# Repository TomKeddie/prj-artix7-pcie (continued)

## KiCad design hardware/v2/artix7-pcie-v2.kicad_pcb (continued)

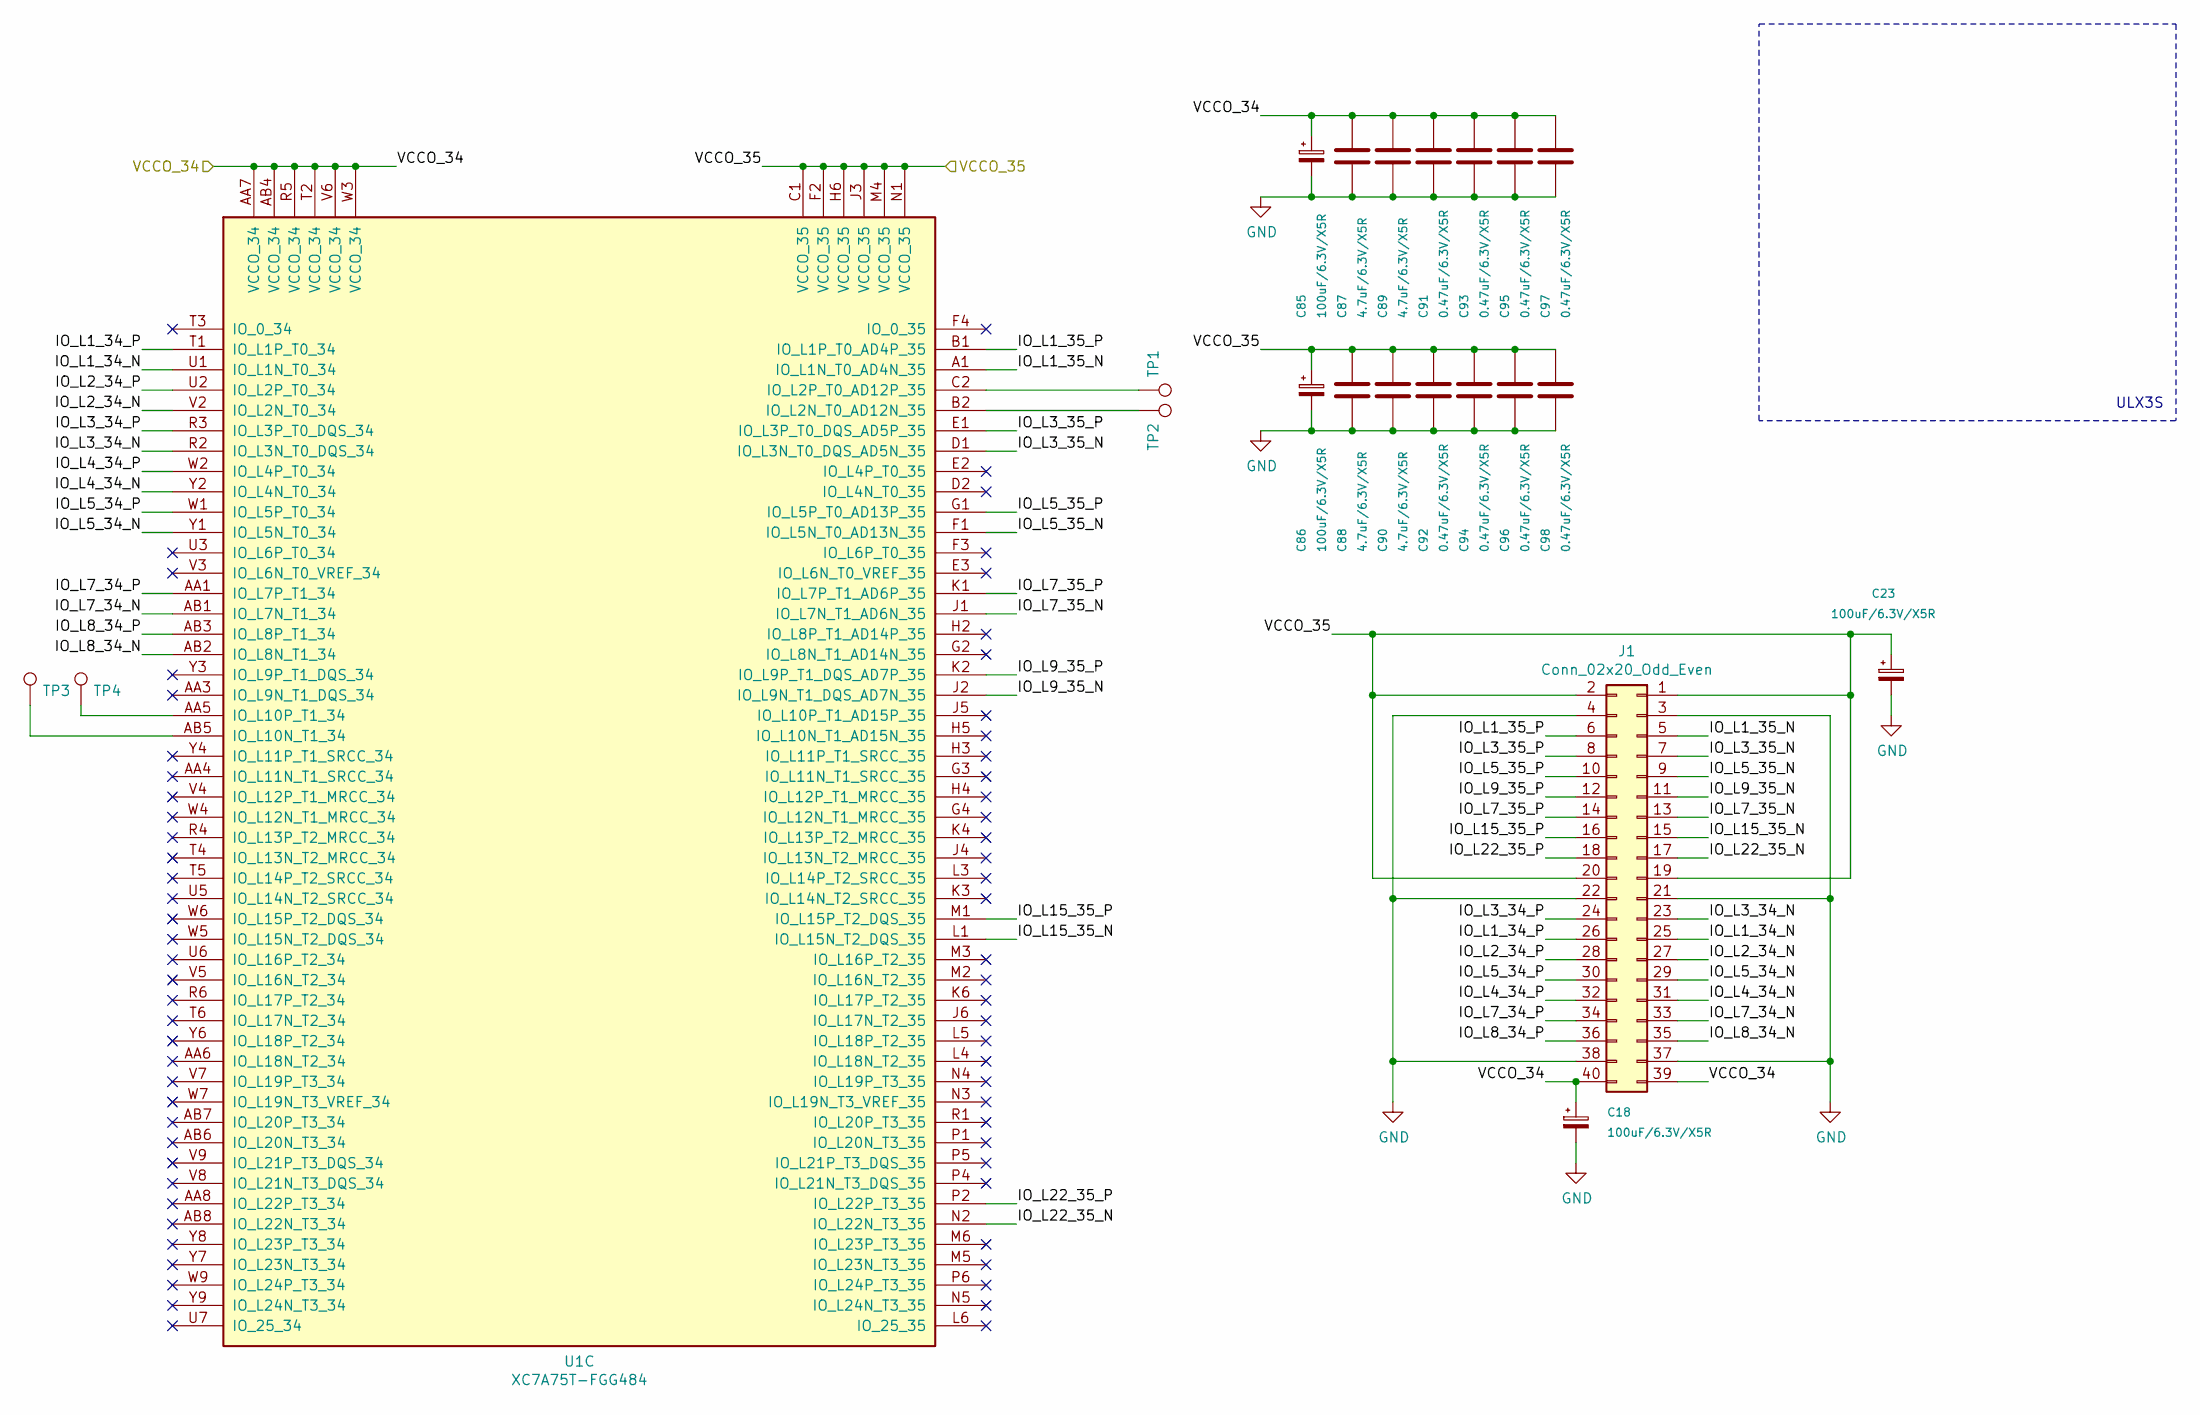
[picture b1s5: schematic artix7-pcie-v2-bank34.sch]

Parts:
C18, C23, C85, C86: 100uF/6.3V/X5R; CP_EIA-3528-15_AVX-H; LCSC C16133
C87, C88, C89, C90: 4.7uF/6.3V/X5R; C_0402_1005Metric; LCSC C23733
C91, C92, C93, C94, C95, C96, C97, C98: 0.47uF/6.3V/X5R; C_0402_1005Metric; LCSC C47339
J1: Conn_02x20_Odd_Even; Socket_Strip_Angled_2x20; LCSC DNP
TP1, TP2, TP3, TP4: TestPoint; TestPoint_Pad_D1.5mm; LCSC DNP
U1: XC7A75T-FGG484; Xilinx_FGG484; LCSC DNP

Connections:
/VCCO_34: C18.1, C23.1, C85.1, C86.1, C87.1, C88.1, C89.1, C90.1, C91.1, C92.1, C93.1, C94.1, C95.1, C96.1, C97.1, C98.1, J1.1, J1.2, J1.19, J1.20, J1.39, J1.40, U1.AA7 (VCCO_34), U1.AB4 (VCCO_34), U1.C1 (VCCO_35), U1.F2 (VCCO_35), U1.H6 (VCCO_35), U1.J3 (VCCO_35), U1.M4 (VCCO_35), U1.N1 (VCCO_35), U1.R5 (VCCO_34), U1.T2 (VCCO_34), U1.V6 (VCCO_34), U1.W3 (VCCO_34); also elsewhere on the board
/artix7-pcie-v2-bank34/IO_L1_34_N: J1.25, U1.U1 (IO_L1N_T0_34)
/artix7-pcie-v2-bank34/IO_L1_34_P: J1.26, U1.T1 (IO_L1P_T0_34)
/artix7-pcie-v2-bank34/IO_L1_35_N: J1.5, U1.A1 (IO_L1N_T0_AD4N_35)
/artix7-pcie-v2-bank34/IO_L1_35_P: J1.6, U1.B1 (IO_L1P_T0_AD4P_35)
/artix7-pcie-v2-bank34/IO_L2_34_N: J1.27, U1.V2 (IO_L2N_T0_34)
/artix7-pcie-v2-bank34/IO_L2_34_P: J1.28, U1.U2 (IO_L2P_T0_34)
/artix7-pcie-v2-bank34/IO_L3_34_N: J1.23, U1.R2 (IO_L3N_T0_DQS_34)
/artix7-pcie-v2-bank34/IO_L3_34_P: J1.24, U1.R3 (IO_L3P_T0_DQS_34)
/artix7-pcie-v2-bank34/IO_L3_35_N: J1.7, U1.D1 (IO_L3N_T0_DQS_AD5N_35)
/artix7-pcie-v2-bank34/IO_L3_35_P: J1.8, U1.E1 (IO_L3P_T0_DQS_AD5P_35)
/artix7-pcie-v2-bank34/IO_L4_34_N: J1.31, U1.Y2 (IO_L4N_T0_34)
/artix7-pcie-v2-bank34/IO_L4_34_P: J1.32, U1.W2 (IO_L4P_T0_34)
/artix7-pcie-v2-bank34/IO_L5_34_N: J1.29, U1.Y1 (IO_L5N_T0_34)
/artix7-pcie-v2-bank34/IO_L5_34_P: J1.30, U1.W1 (IO_L5P_T0_34)
/artix7-pcie-v2-bank34/IO_L5_35_N: J1.9, U1.F1 (IO_L5N_T0_AD13N_35)
/artix7-pcie-v2-bank34/IO_L5_35_P: J1.10, U1.G1 (IO_L5P_T0_AD13P_35)
/artix7-pcie-v2-bank34/IO_L7_34_N: J1.33, U1.AB1 (IO_L7N_T1_34)
/artix7-pcie-v2-bank34/IO_L7_34_P: J1.34, U1.AA1 (IO_L7P_T1_34)
/artix7-pcie-v2-bank34/IO_L7_35_N: J1.13, U1.J1 (IO_L7N_T1_AD6N_35)
/artix7-pcie-v2-bank34/IO_L7_35_P: J1.14, U1.K1 (IO_L7P_T1_AD6P_35)
/artix7-pcie-v2-bank34/IO_L8_34_N: J1.35, U1.AB2 (IO_L8N_T1_34)
/artix7-pcie-v2-bank34/IO_L8_34_P: J1.36, U1.AB3 (IO_L8P_T1_34)
/artix7-pcie-v2-bank34/IO_L9_35_N: J1.11, U1.J2 (IO_L9N_T1_DQS_AD7N_35)
/artix7-pcie-v2-bank34/IO_L9_35_P: J1.12, U1.K2 (IO_L9P_T1_DQS_AD7P_35)
/artix7-pcie-v2-bank34/IO_L15_35_N: J1.15, U1.L1 (IO_L15N_T2_DQS_35)
/artix7-pcie-v2-bank34/IO_L15_35_P: J1.16, U1.M1 (IO_L15P_T2_DQS_35)
/artix7-pcie-v2-bank34/IO_L22_35_N: J1.17, U1.N2 (IO_L22N_T3_35)
/artix7-pcie-v2-bank34/IO_L22_35_P: J1.18, U1.P2 (IO_L22P_T3_35)
GND: C18.2, C23.2, C85.2, C86.2, C87.2, C88.2, C89.2, C90.2, C91.2, C92.2, C93.2, C94.2, C95.2, C96.2, C97.2, C98.2, J1.3, J1.4, J1.21, J1.22, J1.37, J1.38; also elsewhere on the board
unnamed: TP1.1, U1.C2 (IO_L2P_T0_AD12P_35)
unnamed: TP2.1, U1.B2 (IO_L2N_T0_AD12N_35)
unnamed: TP3.1, U1.AB5 (IO_L10N_T1_34)
unnamed: TP4.1, U1.AA5 (IO_L10P_T1_34)

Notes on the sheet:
ULX3S

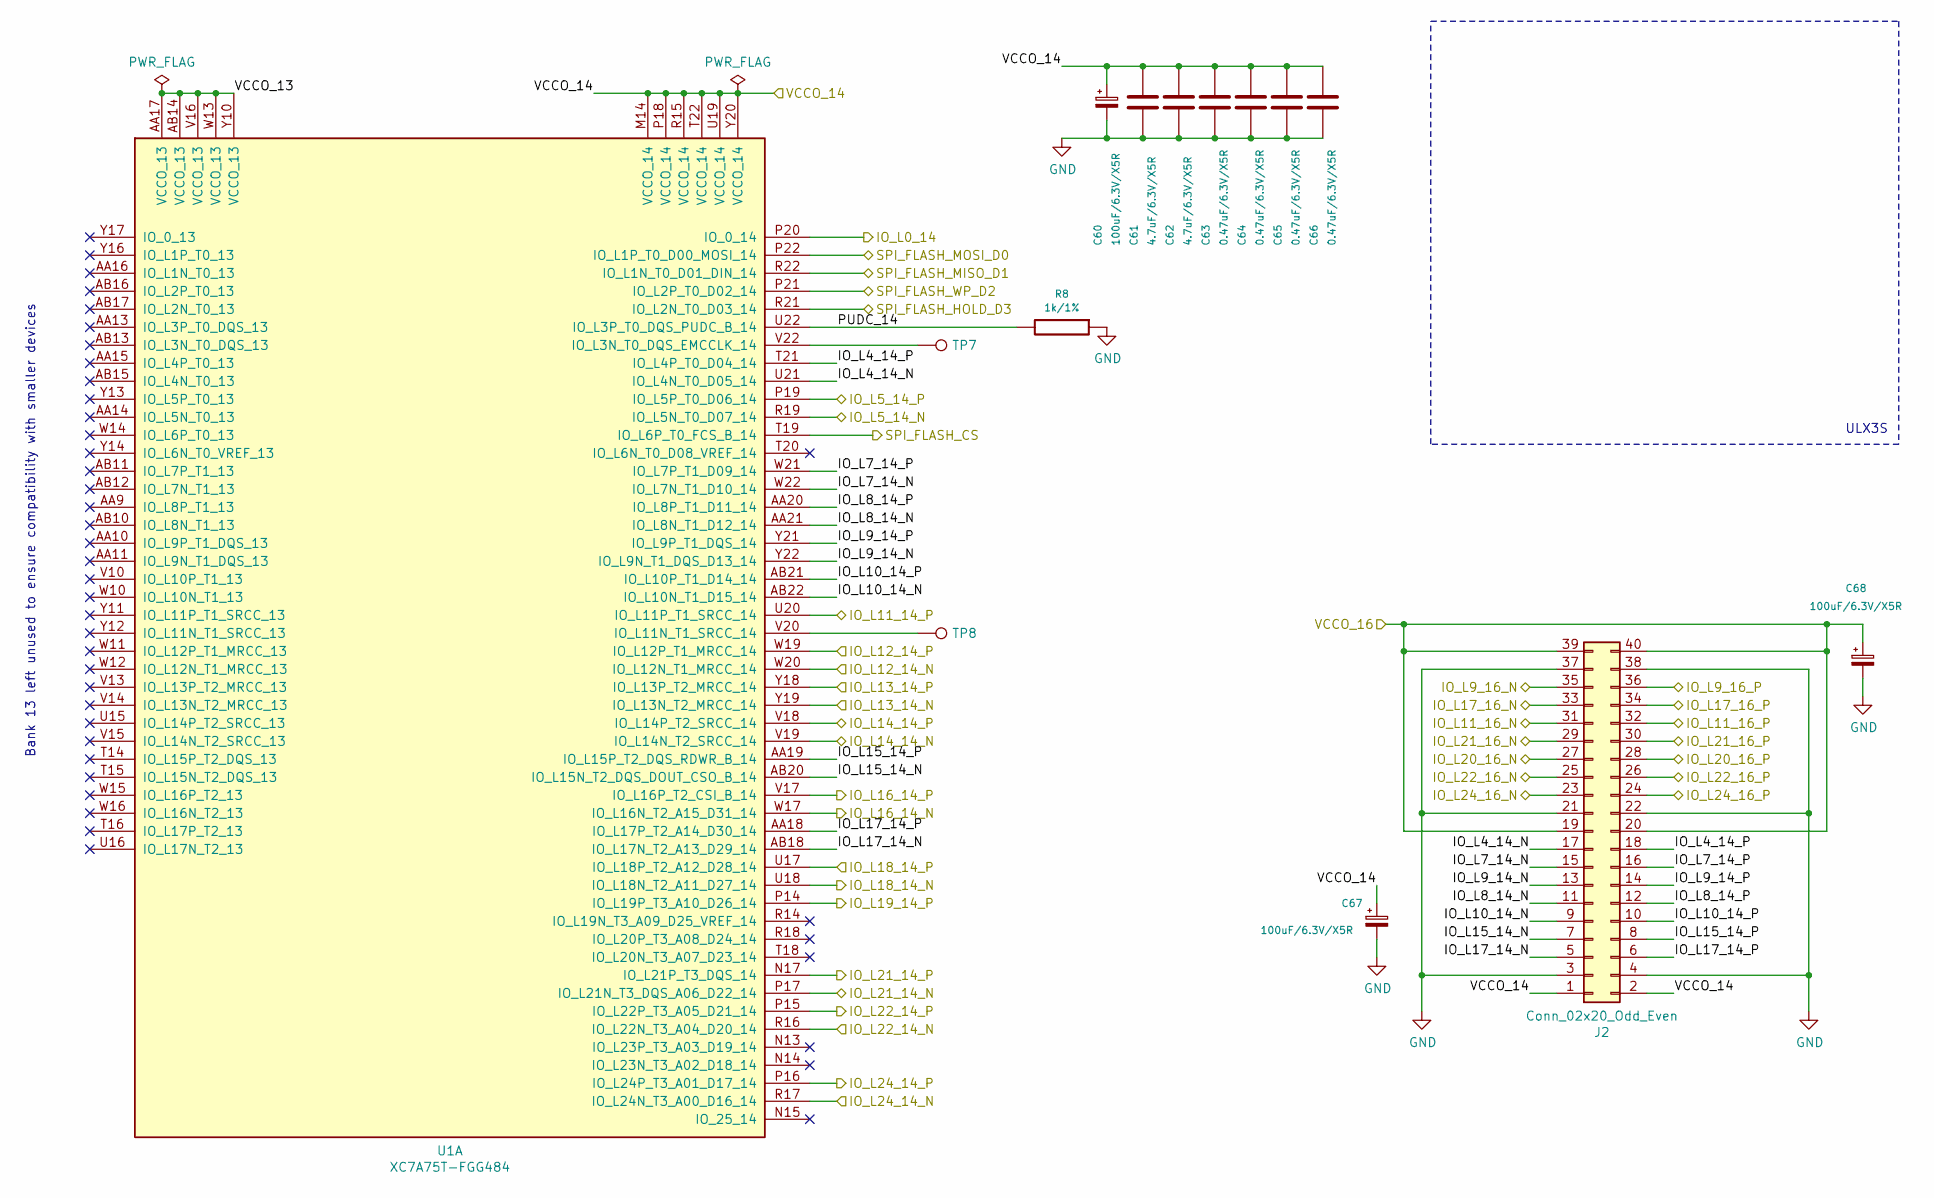
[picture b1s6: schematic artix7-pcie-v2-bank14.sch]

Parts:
C60, C67, C68: 100uF/6.3V/X5R; CP_EIA-3528-15_AVX-H; LCSC C16133
C61, C62: 4.7uF/6.3V/X5R; C_0402_1005Metric; LCSC C23733
C63, C64, C65, C66: 0.47uF/6.3V/X5R; C_0402_1005Metric; LCSC C47339
J2: Conn_02x20_Odd_Even; Socket_Strip_Angled_2x20; LCSC DNP
R8: 1k/1%; R_0402_1005Metric; LCSC C11702
TP7, TP8: TestPoint; TestPoint_Pad_D1.5mm; LCSC DNP
U1: XC7A75T-FGG484; Xilinx_FGG484; LCSC DNP

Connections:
+3V3: C60.1, C61.1, C62.1, C63.1, C64.1, C65.1, C66.1, C67.1, J2.1, J2.2, U1.M14 (VCCO_14), U1.P18 (VCCO_14), U1.R15 (VCCO_14), U1.T22 (VCCO_14), U1.U19 (VCCO_14), U1.Y20 (VCCO_14); also elsewhere on the board
/CFG_FLASH_CS: U1.T19 (IO_L6P_T0_FCS_B_14); also elsewhere on the board
/CFG_FLASH_HOLD_D3: U1.R21 (IO_L2N_T0_D03_14); also elsewhere on the board
/CFG_FLASH_MISO_D1: U1.R22 (IO_L1N_T0_D01_DIN_14); also elsewhere on the board
/CFG_FLASH_MOSI_D0: U1.P22 (IO_L1P_T0_D00_MOSI_14); also elsewhere on the board
/CFG_FLASH_WP_D2: U1.P21 (IO_L2P_T0_D02_14); also elsewhere on the board
/CLKIN_N: U1.Y19 (IO_L13N_T2_MRCC_14); also elsewhere on the board
/CLKIN_P: U1.Y18 (IO_L13P_T2_MRCC_14); also elsewhere on the board
/CLK_SCL: U1.N17 (IO_L21P_T3_DQS_14); also elsewhere on the board
/CLK_SDA: U1.P17 (IO_L21N_T3_DQS_A06_D22_14); also elsewhere on the board
/PCIE_PERST: U1.R17 (IO_L24N_T3_A00_D16_14); also elsewhere on the board
/PCIE_WAKE: U1.R16 (IO_L22N_T3_A04_D20_14); also elsewhere on the board
/S0_USB2_N: U1.R19 (IO_L5N_T0_D07_14); also elsewhere on the board
/S0_USB2_P: U1.P19 (IO_L5P_T0_D06_14); also elsewhere on the board
/S0_USB2_PULLUP: U1.P20 (IO_0_14); also elsewhere on the board
/VCCO_16: C68.1, J2.19, J2.20, J2.39, J2.40; also elsewhere on the board
/artix7-pcie-v2-bank14/IO_L4_14_N: J2.17, U1.U21 (IO_L4N_T0_D05_14)
/artix7-pcie-v2-bank14/IO_L4_14_P: J2.18, U1.T21 (IO_L4P_T0_D04_14)
/artix7-pcie-v2-bank14/IO_L7_14_N: J2.15, U1.W22 (IO_L7N_T1_D10_14)
/artix7-pcie-v2-bank14/IO_L7_14_P: J2.16, U1.W21 (IO_L7P_T1_D09_14)
/artix7-pcie-v2-bank14/IO_L8_14_N: J2.11, U1.AA21 (IO_L8N_T1_D12_14)
/artix7-pcie-v2-bank14/IO_L8_14_P: J2.12, U1.AA20 (IO_L8P_T1_D11_14)
/artix7-pcie-v2-bank14/IO_L9_14_N: J2.13, U1.Y22 (IO_L9N_T1_DQS_D13_14)
/artix7-pcie-v2-bank14/IO_L9_14_P: J2.14, U1.Y21 (IO_L9P_T1_DQS_14)
/artix7-pcie-v2-bank14/IO_L9_16_N: J2.35; also elsewhere on the board
/artix7-pcie-v2-bank14/IO_L9_16_P: J2.36; also elsewhere on the board
/artix7-pcie-v2-bank14/IO_L10_14_N: J2.9, U1.AB22 (IO_L10N_T1_D15_14)
/artix7-pcie-v2-bank14/IO_L10_14_P: J2.10, U1.AB21 (IO_L10P_T1_D14_14)
/artix7-pcie-v2-bank14/IO_L11_14_P: U1.U20 (IO_L11P_T1_SRCC_14); also elsewhere on the board
/artix7-pcie-v2-bank14/IO_L11_16_N: J2.31; also elsewhere on the board
/artix7-pcie-v2-bank14/IO_L11_16_P: J2.32; also elsewhere on the board
/artix7-pcie-v2-bank14/IO_L12_14_N: U1.W20 (IO_L12N_T1_MRCC_14); also elsewhere on the board
/artix7-pcie-v2-bank14/IO_L12_14_P: U1.W19 (IO_L12P_T1_MRCC_14); also elsewhere on the board
/artix7-pcie-v2-bank14/IO_L14_14_N: U1.V19 (IO_L14N_T2_SRCC_14); also elsewhere on the board
/artix7-pcie-v2-bank14/IO_L14_14_P: U1.V18 (IO_L14P_T2_SRCC_14); also elsewhere on the board
/artix7-pcie-v2-bank14/IO_L15_14_N: J2.7, U1.AB20 (IO_L15N_T2_DQS_DOUT_CSO_B_14)
/artix7-pcie-v2-bank14/IO_L15_14_P: J2.8, U1.AA19 (IO_L15P_T2_DQS_RDWR_B_14)
/artix7-pcie-v2-bank14/IO_L16_14_N: U1.W17 (IO_L16N_T2_A15_D31_14); also elsewhere on the board
/artix7-pcie-v2-bank14/IO_L16_14_P: U1.V17 (IO_L16P_T2_CSI_B_14); also elsewhere on the board
/artix7-pcie-v2-bank14/IO_L17_14_N: J2.5, U1.AB18 (IO_L17N_T2_A13_D29_14)
/artix7-pcie-v2-bank14/IO_L17_14_P: J2.6, U1.AA18 (IO_L17P_T2_A14_D30_14)
/artix7-pcie-v2-bank14/IO_L17_16_N: J2.33; also elsewhere on the board
/artix7-pcie-v2-bank14/IO_L17_16_P: J2.34; also elsewhere on the board
/artix7-pcie-v2-bank14/IO_L18_14_N: U1.U18 (IO_L18N_T2_A11_D27_14); also elsewhere on the board
/artix7-pcie-v2-bank14/IO_L18_14_P: U1.U17 (IO_L18P_T2_A12_D28_14); also elsewhere on the board
/artix7-pcie-v2-bank14/IO_L19_14_P: U1.P14 (IO_L19P_T3_A10_D26_14); also elsewhere on the board
/artix7-pcie-v2-bank14/IO_L20_16_N: J2.27; also elsewhere on the board
/artix7-pcie-v2-bank14/IO_L20_16_P: J2.28; also elsewhere on the board
/artix7-pcie-v2-bank14/IO_L21_16_N: J2.29; also elsewhere on the board
/artix7-pcie-v2-bank14/IO_L21_16_P: J2.30; also elsewhere on the board
/artix7-pcie-v2-bank14/IO_L22_14_P: U1.P15 (IO_L22P_T3_A05_D21_14); also elsewhere on the board
/artix7-pcie-v2-bank14/IO_L22_16_N: J2.25; also elsewhere on the board
/artix7-pcie-v2-bank14/IO_L22_16_P: J2.26; also elsewhere on the board
/artix7-pcie-v2-bank14/IO_L24_14_P: U1.P16 (IO_L24P_T3_A01_D17_14); also elsewhere on the board
/artix7-pcie-v2-bank14/IO_L24_16_N: J2.23; also elsewhere on the board
/artix7-pcie-v2-bank14/IO_L24_16_P: J2.24; also elsewhere on the board
/artix7-pcie-v2-bank14/PUDC_14: R8.2, U1.U22 (IO_L3P_T0_DQS_PUDC_B_14)
/artix7-pcie-v2-bank14/VCCO_13: U1.AA17 (VCCO_13), U1.AB14 (VCCO_13), U1.V16 (VCCO_13), U1.W13 (VCCO_13), U1.Y10 (VCCO_13)
GND: C60.2, C61.2, C62.2, C63.2, C64.2, C65.2, C66.2, C67.2, C68.2, J2.3, J2.4, J2.21, J2.22, J2.37, J2.38, R8.1; also elsewhere on the board
unnamed: TP7.1, U1.V22 (IO_L3N_T0_DQS_EMCCLK_14)
unnamed: TP8.1, U1.V20 (IO_L11N_T1_SRCC_14)

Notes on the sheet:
Bank 13 left unused to ensure compatibility with smaller devices
ULX3S

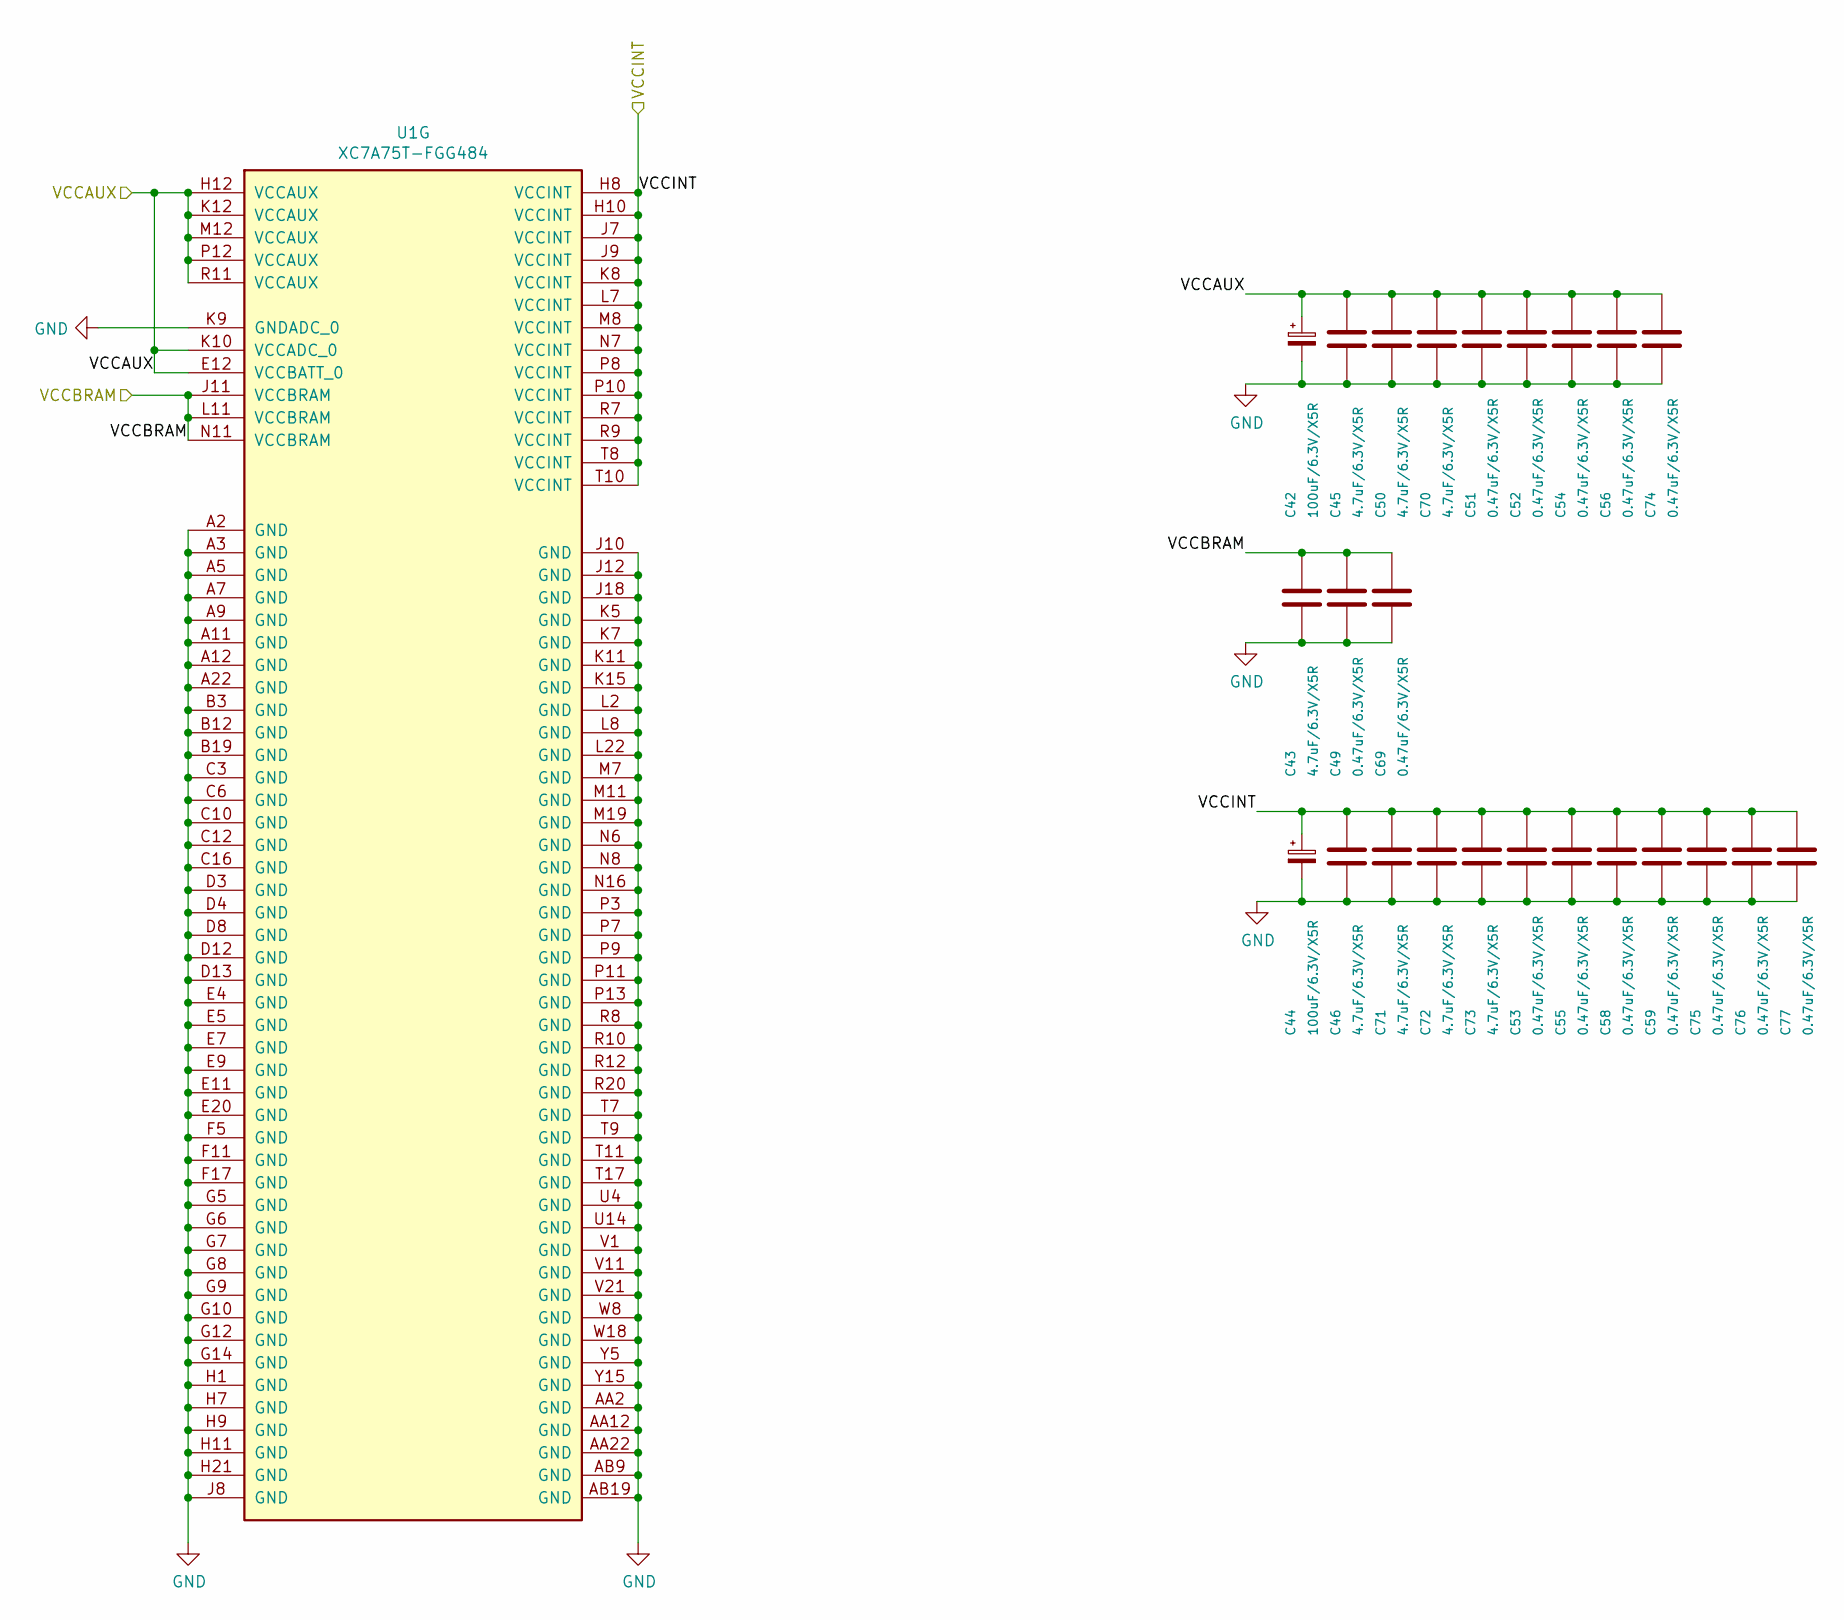
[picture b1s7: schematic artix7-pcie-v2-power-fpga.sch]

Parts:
C42, C44: 100uF/6.3V/X5R; CP_EIA-3528-15_AVX-H; LCSC C16133
C43, C45, C46, C50, C70, C71, C72, C73: 4.7uF/6.3V/X5R; C_0402_1005Metric; LCSC C23733
C49, C51, C52, C53, C54, C55, C56, C58, C59, C69, C74, C75, C76, C77: 0.47uF/6.3V/X5R; C_0402_1005Metric; LCSC C47339
U1: XC7A75T-FGG484; Xilinx_FGG484; LCSC DNP

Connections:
+1V0: C44.1, C46.1, C53.1, C55.1, C58.1, C59.1, C71.1, C72.1, C73.1, C75.1, C76.1, C77.1, U1.H8 (VCCINT), U1.H10 (VCCINT), U1.J7 (VCCINT), U1.J9 (VCCINT), U1.K8 (VCCINT), U1.L7 (VCCINT), U1.M8 (VCCINT), U1.N7 (VCCINT), U1.P8 (VCCINT), U1.P10 (VCCINT), U1.R7 (VCCINT), U1.R9 (VCCINT), U1.T8 (VCCINT), U1.T10 (VCCINT); also elsewhere on the board
+1V8: C42.1, C45.1, C50.1, C51.1, C52.1, C54.1, C56.1, C70.1, C74.1, U1.E12 (VCCBATT_0), U1.H12 (VCCAUX), U1.K10 (VCCADC_0), U1.K12 (VCCAUX), U1.M12 (VCCAUX), U1.P12 (VCCAUX), U1.R11 (VCCAUX); also elsewhere on the board
/Power/VCCBRAM: C43.1, C49.1, C69.1, U1.J11 (VCCBRAM), U1.L11 (VCCBRAM), U1.N11 (VCCBRAM); also elsewhere on the board
GND: C42.2, C43.2, C44.2, C45.2, C46.2, C49.2, C50.2, C51.2, C52.2, C53.2, C54.2, C55.2, C56.2, C58.2, C59.2, C69.2, C70.2, C71.2, C72.2, C73.2, C74.2, C75.2, C76.2, C77.2, U1.A2 (GND), U1.A3 (GND), U1.A5 (GND), U1.A7 (GND), U1.A9 (GND), U1.A11 (GND), U1.A12 (GND), U1.A22 (GND), U1.AA2 (GND), U1.AA12 (GND), U1.AA22 (GND), U1.AB9 (GND), U1.AB19 (GND), U1.B3 (GND), U1.B12 (GND), U1.B19 (GND), U1.C3 (GND), U1.C6 (GND), U1.C10 (GND), U1.C12 (GND), U1.C16 (GND), U1.D3 (GND), U1.D4 (GND), U1.D8 (GND), U1.D12 (GND), U1.D13 (GND), U1.E4 (GND), U1.E5 (GND), U1.E7 (GND), U1.E9 (GND), U1.E11 (GND), U1.E20 (GND), U1.F5 (GND), U1.F11 (GND), U1.F17 (GND), U1.G5 (GND), U1.G6 (GND), U1.G7 (GND), U1.G8 (GND), U1.G9 (GND), U1.G10 (GND), U1.G12 (GND), U1.G14 (GND), U1.H1 (GND), U1.H7 (GND), U1.H9 (GND), U1.H11 (GND), U1.H21 (GND), U1.J8 (GND), U1.J10 (GND), U1.J12 (GND), U1.J18 (GND), U1.K5 (GND), U1.K7 (GND), U1.K9 (GNDADC_0), U1.K11 (GND), U1.K15 (GND), U1.L2 (GND), U1.L8 (GND), U1.L22 (GND), U1.M7 (GND), U1.M11 (GND), U1.M19 (GND), U1.N6 (GND), U1.N8 (GND), U1.N16 (GND), U1.P3 (GND), U1.P7 (GND), U1.P9 (GND), U1.P11 (GND), U1.P13 (GND), U1.R8 (GND), U1.R10 (GND), U1.R12 (GND), U1.R20 (GND), U1.T7 (GND), U1.T9 (GND), U1.T11 (GND), U1.T17 (GND), U1.U4 (GND), U1.U14 (GND), U1.V1 (GND), U1.V11 (GND), U1.V21 (GND), U1.W8 (GND), U1.W18 (GND), U1.Y5 (GND), U1.Y15 (GND); also elsewhere on the board

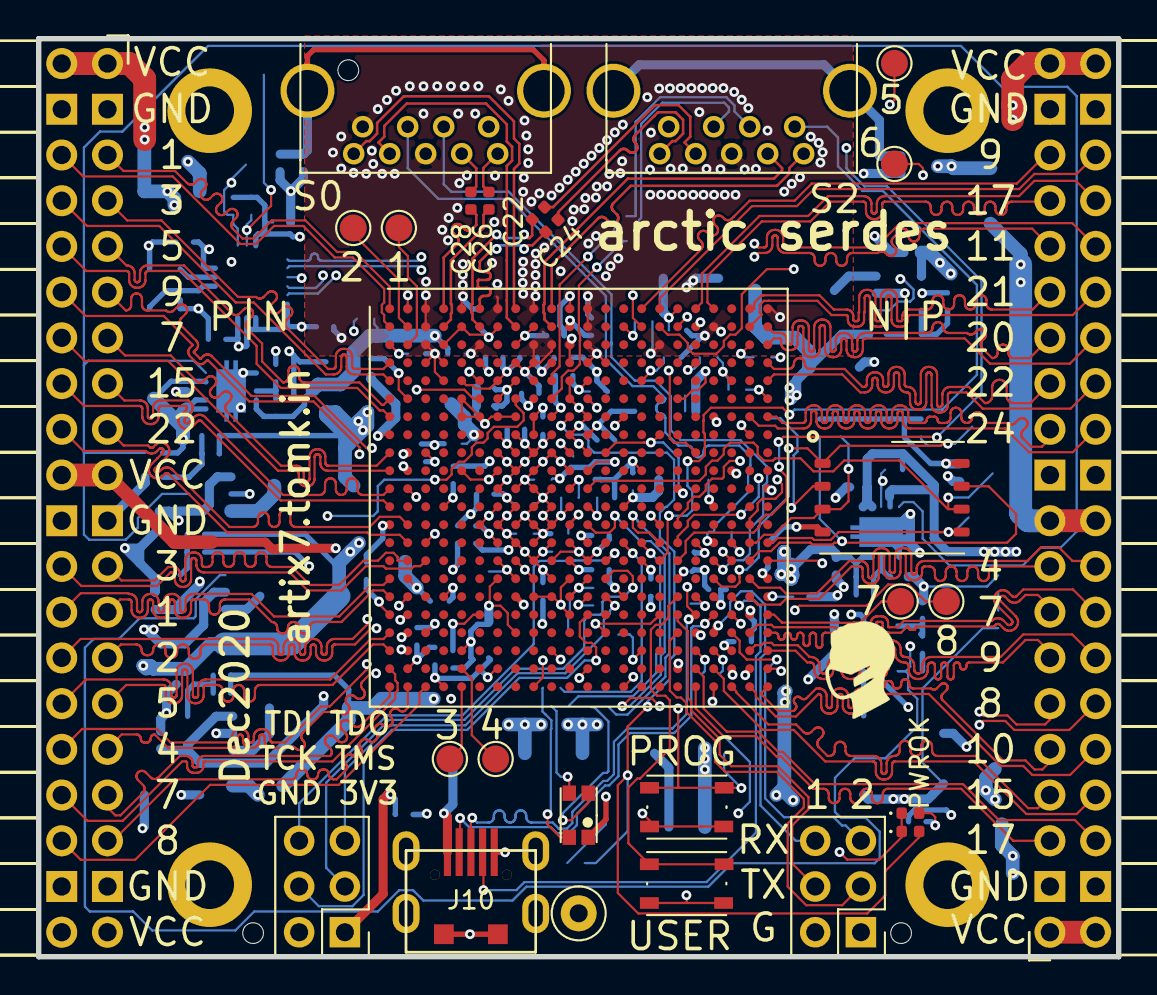
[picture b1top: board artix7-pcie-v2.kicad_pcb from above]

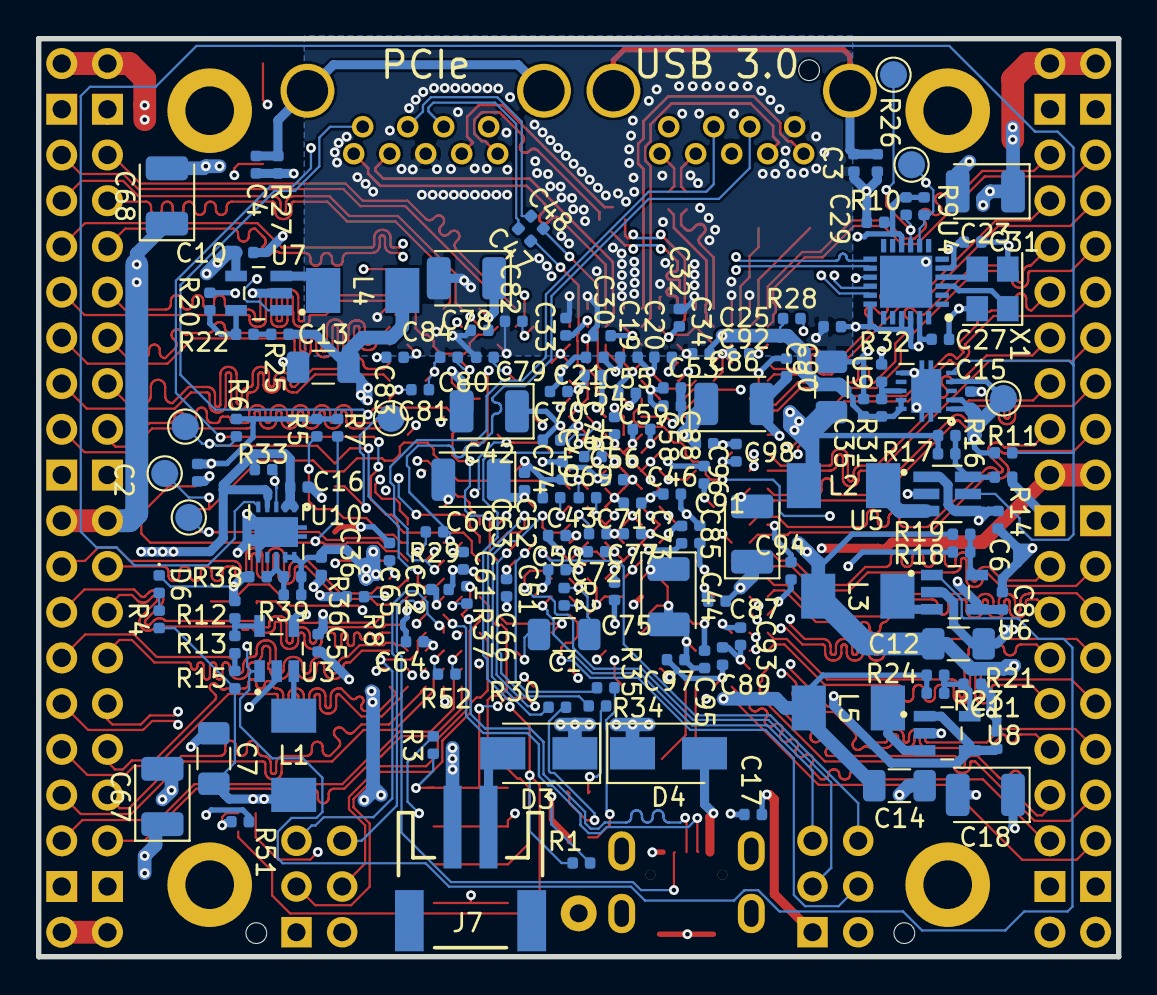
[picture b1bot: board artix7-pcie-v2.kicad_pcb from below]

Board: 4 copper layers, 60.0 x 51.0 mm, 189 parts (154 on the bottom side), 156 nets.

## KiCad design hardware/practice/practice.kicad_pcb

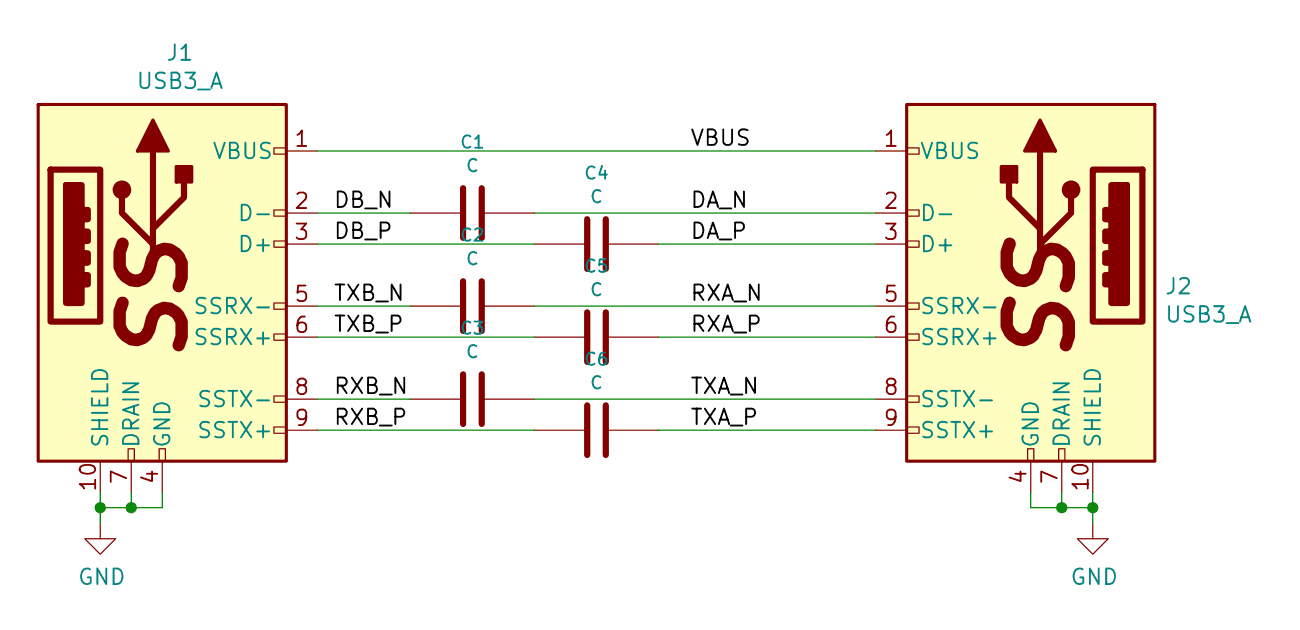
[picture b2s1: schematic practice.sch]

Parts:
C1, C2, C3, C4, C5, C6: C; C_0402_1005Metric
J1, J2: USB3_A; USB3_A_Aliexpress

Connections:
/DA_N: C1.1, J2.2 (D-)
/DA_P: C4.1, J2.3 (D+)
/DB_N: C1.2, J1.2 (D-)
/DB_P: C4.2, J1.3 (D+)
/RXA_N: C2.1, J2.5 (SSRX-)
/RXA_P: C5.1, J2.6 (SSRX+)
/RXB_N: C3.2, J1.8 (SSTX-)
/RXB_P: C6.2, J1.9 (SSTX+)
/TXA_N: C3.1, J2.8 (SSTX-)
/TXA_P: C6.1, J2.9 (SSTX+)
/TXB_N: C2.2, J1.5 (SSRX-)
/TXB_P: C5.2, J1.6 (SSRX+)
/VBUS: J1.1 (VBUS), J2.1 (VBUS)
GND: J1.4 (GND), J1.7 (DRAIN), J1.10 (SHIELD), J2.4 (GND), J2.7 (DRAIN), J2.10 (SHIELD)

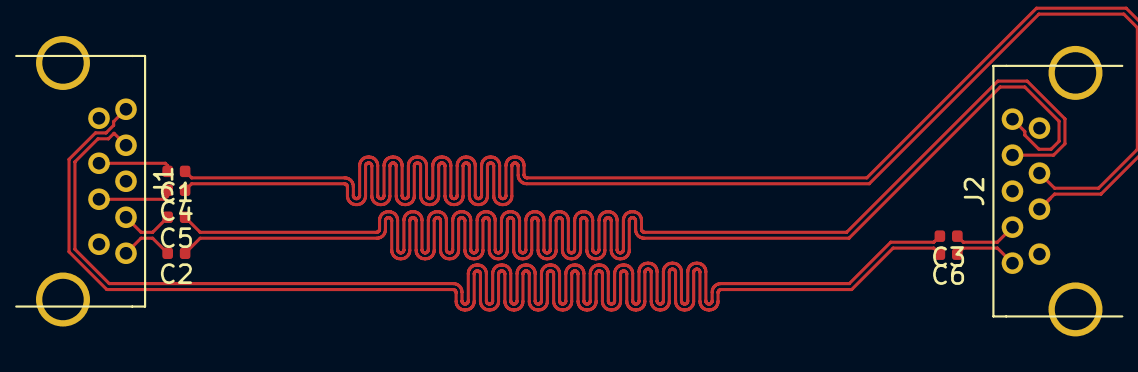
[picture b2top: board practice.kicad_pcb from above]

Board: 4 copper layers, 8 parts (0 on the bottom side), 14 nets.

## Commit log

2018-09-20 Added library symbol for XC7A12T-1CPG238I
2018-09-30 First pass at artix pcie board - serdes
2018-09-30 Artix 7 PCIe test builds
2020-02-13 Prepare for v2, move first attempt to v1
2020-02-13 Add NeTV2 schematic pdf
2020-02-15 v1 updates (abandoned)
2020-02-16 artix7-pcie-v2: added project with partially complete power sheet
2020-02-18 fpga: added netv2 target as local example
2020-03-03 v2 schematic : add config block and connectors
2020-03-03 v2 power schematic : annotated
2020-03-03 v2 schematic: add bank14, serdes, fpga footprint
2020-03-03 v2 schematic: moved 1.0V regulator to APXS006A0X4-SRZ
2020-03-10 sch: moved all power supplies to APXS006A0X4-SRZ
2020-03-10 v2 hardware - all io connectors in schematic
2020-03-15 v2 schematic/pcb: band 13 to NC for smaller device compatibility
2020-03-20 v2 hardware progress checkin, just prior to replacing p/s with TI parts
2020-03-20 Add v2 litex/migen pin planning impl.
2020-03-20 Move v1 fpga code to subdirectory
2020-03-20 Addd kicad settings to gitignore
2020-03-22 v2 pcb/schematic update : drc passing, need to add caps
2020-03-22 fpga/plan : updates to match schematic
2020-03-28 v2 hardware: pcb progress commit, 155 unrouted
2020-03-28 v2 plan.py: add spi, move micro usb to ease routing
2020-04-10 v2 pcb/schematic progress commit, all tough signals routed out
2020-04-12 Add practice schematic/pcb for diff pair routing
2020-04-12 v2 schematic/pcb progress commit - 12 unrouted
2020-04-13 v2 hardware: all tracks routed, erc/drc pass
2020-04-14 v2 hardware progress commit - fixed mounting holes and board edge
2020-04-14 v2 progress commit : serdes lanes all deskewed
2020-04-17 First pass add adding pcie Final schematic updates
2020-04-17 v2 plan hdl: Add GigE on Serdes 0
2020-04-18 v2 gateware: pcie and ethernet in the same serdes
2020-04-19 v2 hardware: J2 differential pairs tuned
2020-04-19 v2 hardware: j2_34 diff pairs matched, fix 0402 resistor packages, dropped paste from DNP resistors
2020-04-19 v2 hardware : update tom-kicad submodules to pick up NoPaste parts
2020-04-19 v2 hardware : add missing mounting holes, all pairs tuned and passing. J1_34_DP0.5/0.5 -> MEETS INTER-PAIR TOLERANCE 0.5000 mm (current delta 0.4093) /artix7-pcie-v2-bank34/IO_L1_34 meets intra-pair 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
2020-04-20 Apr2020 rc1
2020-04-20 v2 hardware: april 2020 rc2 - add teardrops
2020-04-27 v2 hardware : add ibom (stale)
2020-05-22 Replace bom with csv version
2020-05-22 Add kitspace yaml config
2020-05-22 rename bom
2020-05-22 v2 hardware: add Digikey part numbers to schematic and generate bom
2020-05-22 hardware v2: bom fixes
2020-05-28 v2 hardware: Add images of rc2/Apr2020 proto
2020-06-01 hardware v2: fix digikey part number for U3
2020-06-21 hardware v2: fix digikey part number on MGTAVTT regulator
2020-06-27 v2 hardware : add clock files
2020-06-28 v2 hardware : add timing commander files
2020-06-28 Update gitmodules
2020-06-28 Add verilog-i2c module for i2c master
2020-06-29 v2 fpga : add litex-arcticserdes.py
2020-06-29 v2 fpga : Add vivado project for bringup
2020-07-11 v2 hdl: add 2c_init.v to vivado project
2020-07-11 v2 fpga: i2c working on Saleae, need to add stop at the end scl is staying low
2020-07-21 v2 fpga: vivado_1 i2c read working
2020-07-23 v2 fpga: finish clock config with reset sequence
2020-08-01 Add arduino script for programming clock generator
2020-08-02 hardware: add USB 3.0 connector digikey part number
2020-08-04 fpga v2: vivado_1 - J1 verified, fabric clock changed to 50MHz
2020-08-04 fpga v2: move constraints file to common location
2020-08-04 fpga v2: move constraints file for real
2020-08-08 v2 fpga: J1 and J2 pinout checked
2020-08-08 fpga v2: add j2 testing to vivado_1
2020-08-08 v2 fpga: clock config completed by fpga only
2020-08-08 v2 hardware: arduino script for clock config
2020-08-09 v2 hardware: add eye scan images
2020-08-09 v2 hardware : add rc2 bringup images
2020-08-09 v2 hardware: aug2020 pcb updates
2020-08-10 v2 hardware: Aug2020/rc2 version - flip tx/rx pairs on s2 - add lcsc part numbers
    rc2 errata schematic
    - change serial port connector to add +3.3V ? (8-pin)(NO)
    - add test points for flash pre-programming
    - smaller package on input direction diodes (NO)
    - bom dupe errors
    - remove all p/s 0R bringup parts
2020-08-10 v2 hardware : fix isues found by jlcpcb - change 0603 parts to add paste as they are now loaded - fix solder paste/mask issues with TPS power modules
2020-09-02 Added new regulator symbols for updated p/s
2020-09-02 Added new regulator footprints for updated p/s
2020-09-05 JLC power supplies almost routed VCCBRAM to go Need to - check BOM - add power good leds - fix vccbram inc caps - fix 100uF part number - update silk
2020-09-06 v2 hardware updates: fixed inductor footprint, updates for DFA
2020-09-06 v2 hardware: add jlcpcb bom file
2020-09-09 v2 hardare: progress commit on Sept2020 run
2020-09-09 v2 hardware: fixed drc issues from inductor pad changes
2020-09-13 v2 hardware: change 100uF to 3528 for jlcpcb
2020-09-13 Update tom-kicad anchor
2020-09-13 v2 hardware: sep2020 run - fixed issues with parts missing from centroid file
2020-09-18 v2 hardware: fix drc/unrouted ready for resubmission to JLC
2020-09-21 hardware v2: sep2020 as submitted to jlcpcb
2020-09-23 hardware v2: add jlcpcb rotation images
2020-11-22 hardware: update pcb as per sep 2020b
2020-11-22 Re-route HS diff pairs for 90R (0.147/0.253 as per RPI cm4 carrier) Add ground stitching
2020-11-22 hardware: minor fixes to v2 for Nov2020 run
2020-12-10 v2 hardware: add ground pours to power layer
2020-12-11 v2 hardware: fix issues with pwr layer copper pour, add Dec2020 release
2021-02-06 Add kibot config file
2021-02-08 hardware: add/update kibot yaml file
